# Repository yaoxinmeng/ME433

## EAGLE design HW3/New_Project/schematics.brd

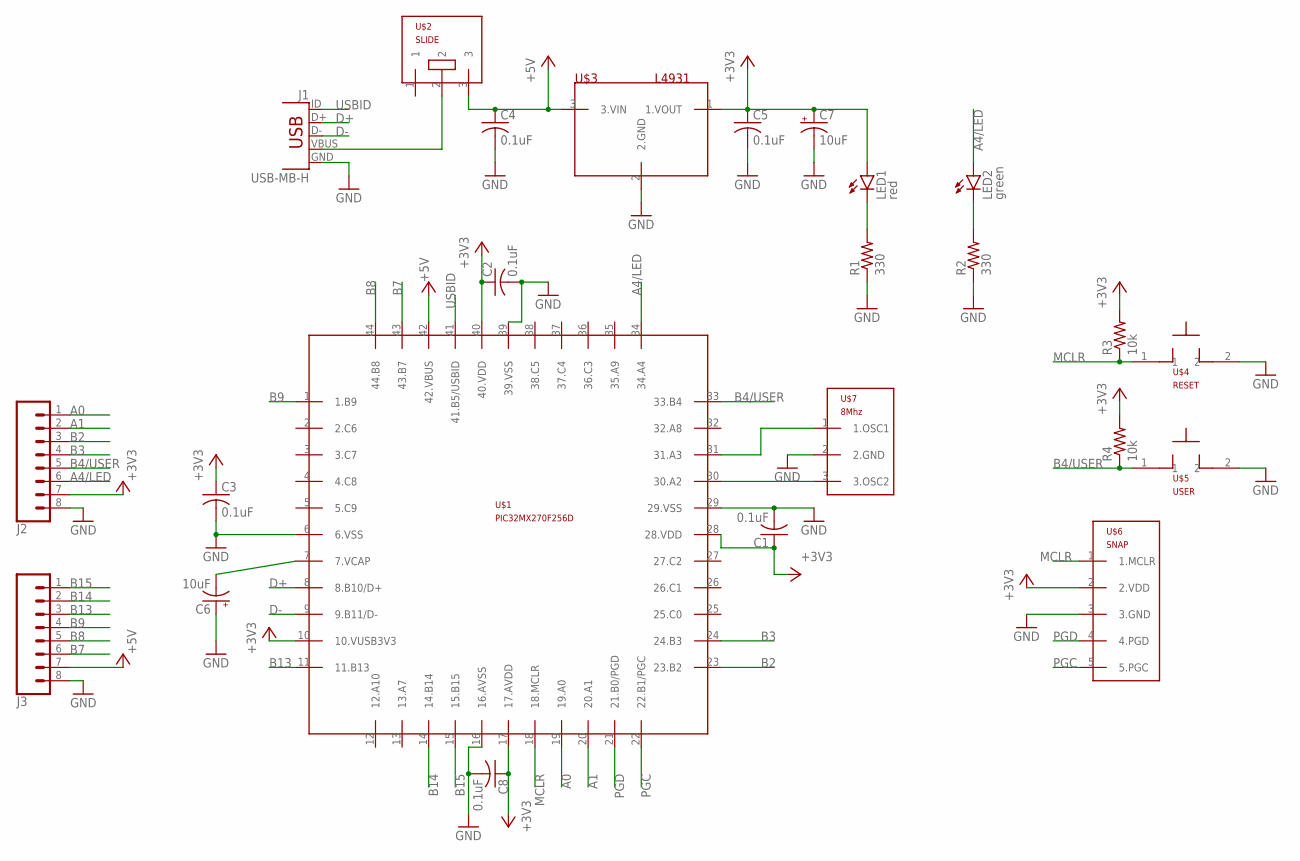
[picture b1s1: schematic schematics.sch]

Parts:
C1, C2, C3, C4, C5, C8: 0.1uF; C025-025X050
C6, C7: 10uF; B45181B
J1: USB-MB-H
J2, J3: CONN_08"; 1X08
LED1: red; LED3MM
LED2: green; LED3MM
R1, R2: 330; 0207/10
R3, R4: 10k; 0207/10
U$1: PIC32MX270F256D; TQFP44
U$2: SLIDE
U$3: L4931; TO92
U$4: RESET; PB
U$5: USER; PB
U$6: SNAP
U$7: 8Mhz; OSC

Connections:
+3V3: C1.1, C2.1, C3.1, C5.1, C7.+, C8.1, J2.7, LED1.A, R3.2, R4.2, U$1.10 (10.VUSB3V3), U$1.17 (17.AVDD), U$1.28 (28.VDD), U$1.40 (40.VDD), U$3.1 (1.VOUT), U$6.2 (2.VDD)
+5V: C4.1, J3.7, U$1.42 (42.VBUS), U$2.3, U$3.3 (3.VIN)
A0: J2.1, U$1.19 (19.A0)
A1: J2.2, U$1.20 (20.A1)
A4/LED: J2.6, LED2.A, U$1.34 (34.A4)
B2: J2.3, U$1.23 (23.B2)
B3: J2.4, U$1.24 (24.B3)
B4/USER: J2.5, R4.1, U$1.33 (33.B4), U$5.1
B7: J3.6, U$1.43 (43.B7)
B8: J3.5, U$1.44 (44.B8)
B9: J3.4, U$1.1 (1.B9)
B13: J3.3, U$1.11 (11.B13)
B14: J3.2, U$1.14 (14.B14)
B15: J3.1, U$1.15 (15.B15)
D+: J1.D+, U$1.8 (8.B10/D+)
D-: J1.D-, U$1.9 (9.B11/D-)
GND: C1.2, C2.2, C3.2, C4.2, C5.2, C6.+, C7.-, C8.2, J1.GND, J2.8, J3.8, R1.1, R2.1, U$1.6 (6.VSS), U$1.16 (16.AVSS), U$1.29 (29.VSS), U$1.39 (39.VSS), U$3.2 (2.GND), U$4.2, U$5.2, U$6.3 (3.GND), U$7.2 (2.GND)
MCLR: R3.1, U$1.18 (18.MCLR), U$4.1, U$6.1 (1.MCLR)
unnamed: C6.-, U$1.7 (7.VCAP)
unnamed: J1.VBUS, U$2.2
unnamed: LED2.K (C), R2.2
unnamed: LED1.K (C), R1.2
unnamed: U$1.30 (30.A2), U$7.3 (3.OSC2)
unnamed: U$1.31 (31.A3), U$7.1 (1.OSC1)
PGC: U$1.22 (22.B1/PGC), U$6.5 (5.PGC)
PGD: U$1.21 (21.B0/PGD), U$6.4 (4.PGD)
USBID: J1.ID, U$1.41 (41.B5/USBID)

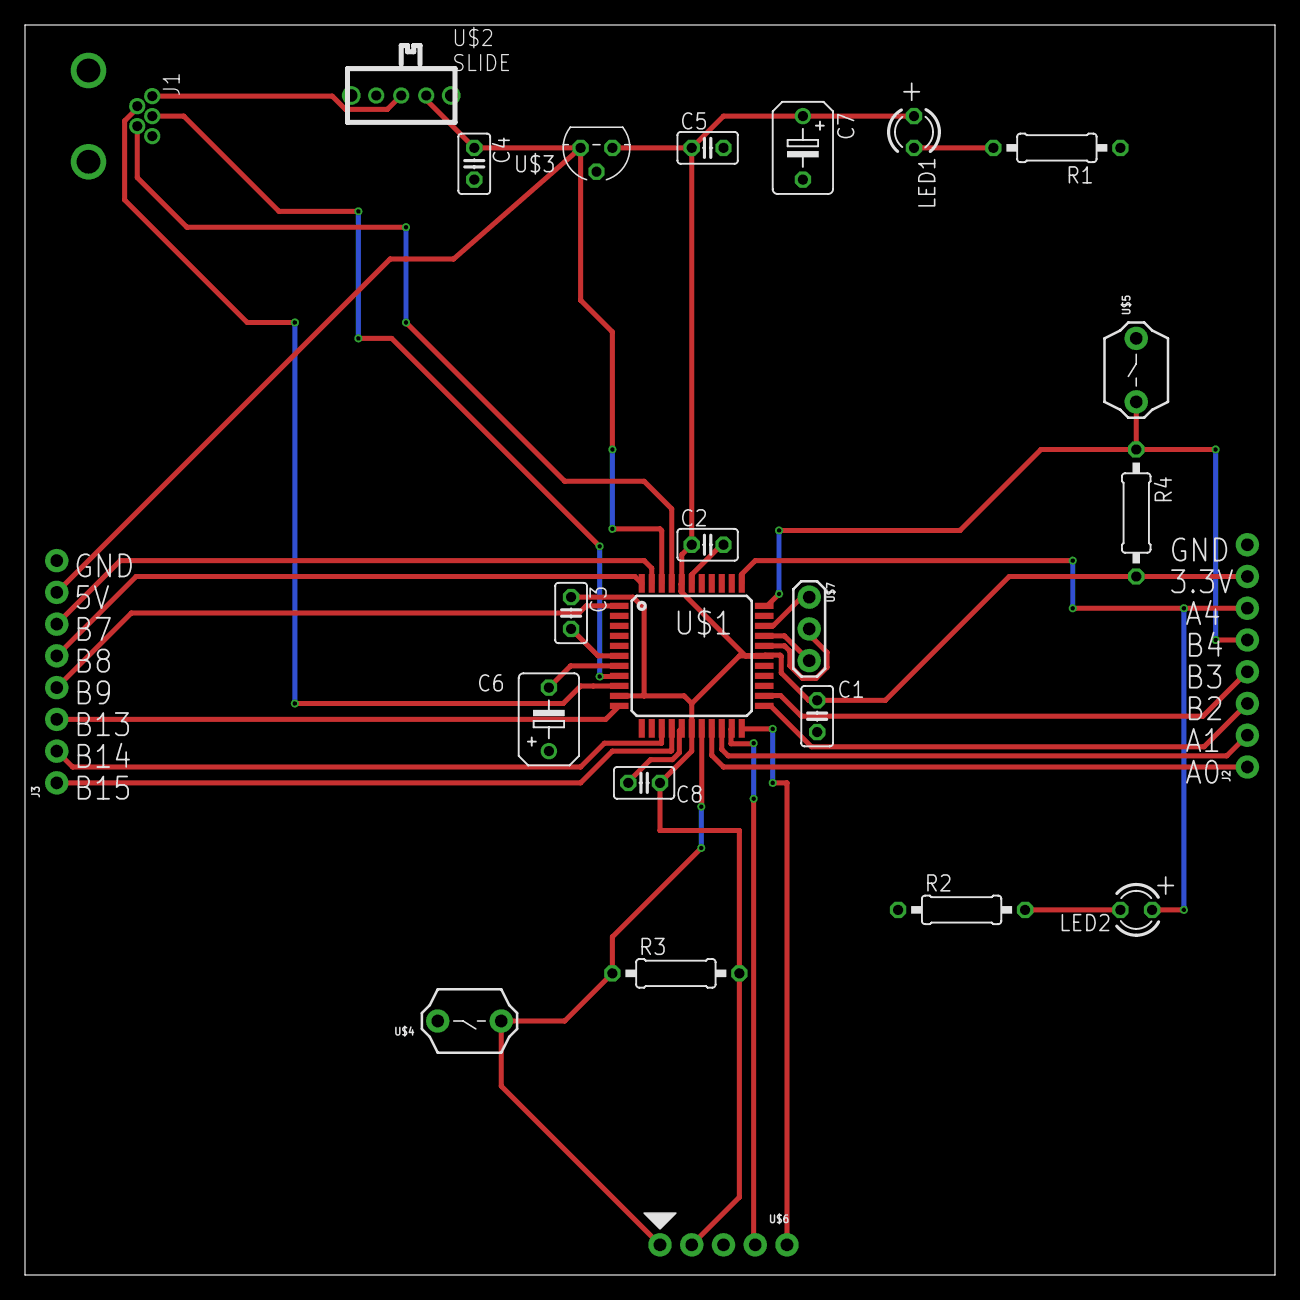
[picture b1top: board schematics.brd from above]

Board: 2 copper layers, 100.0 x 100.0 mm, 24 parts (0 on the bottom side), 27 nets.

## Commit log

2019-04-02 Initialisation
2019-04-03 Update
    most files uploaded
2019-04-03 Sorting
2019-04-03 final
2019-04-09 final update
2019-04-10 Reorganising
    HW2 board is transferred to HW3
2019-04-12 initial
2019-04-12 final change
2019-04-17 HW5 initial
2019-04-17 final HW4
2019-04-19 final HW6
2019-04-24 HW7 final
2019-05-02 HW9 initial
2019-05-02 HW9 final
2019-05-02 HW9 vid
2019-05-02 HW10 initial
2019-05-02 HW10 final
2019-05-02 reorganise HW10
2019-05-08 hw11+hw9
2019-05-09 HW12
2019-05-14 hw11 plot
2019-05-22 Hw14
2019-05-29 HW15
2019-05-29 update HW15
